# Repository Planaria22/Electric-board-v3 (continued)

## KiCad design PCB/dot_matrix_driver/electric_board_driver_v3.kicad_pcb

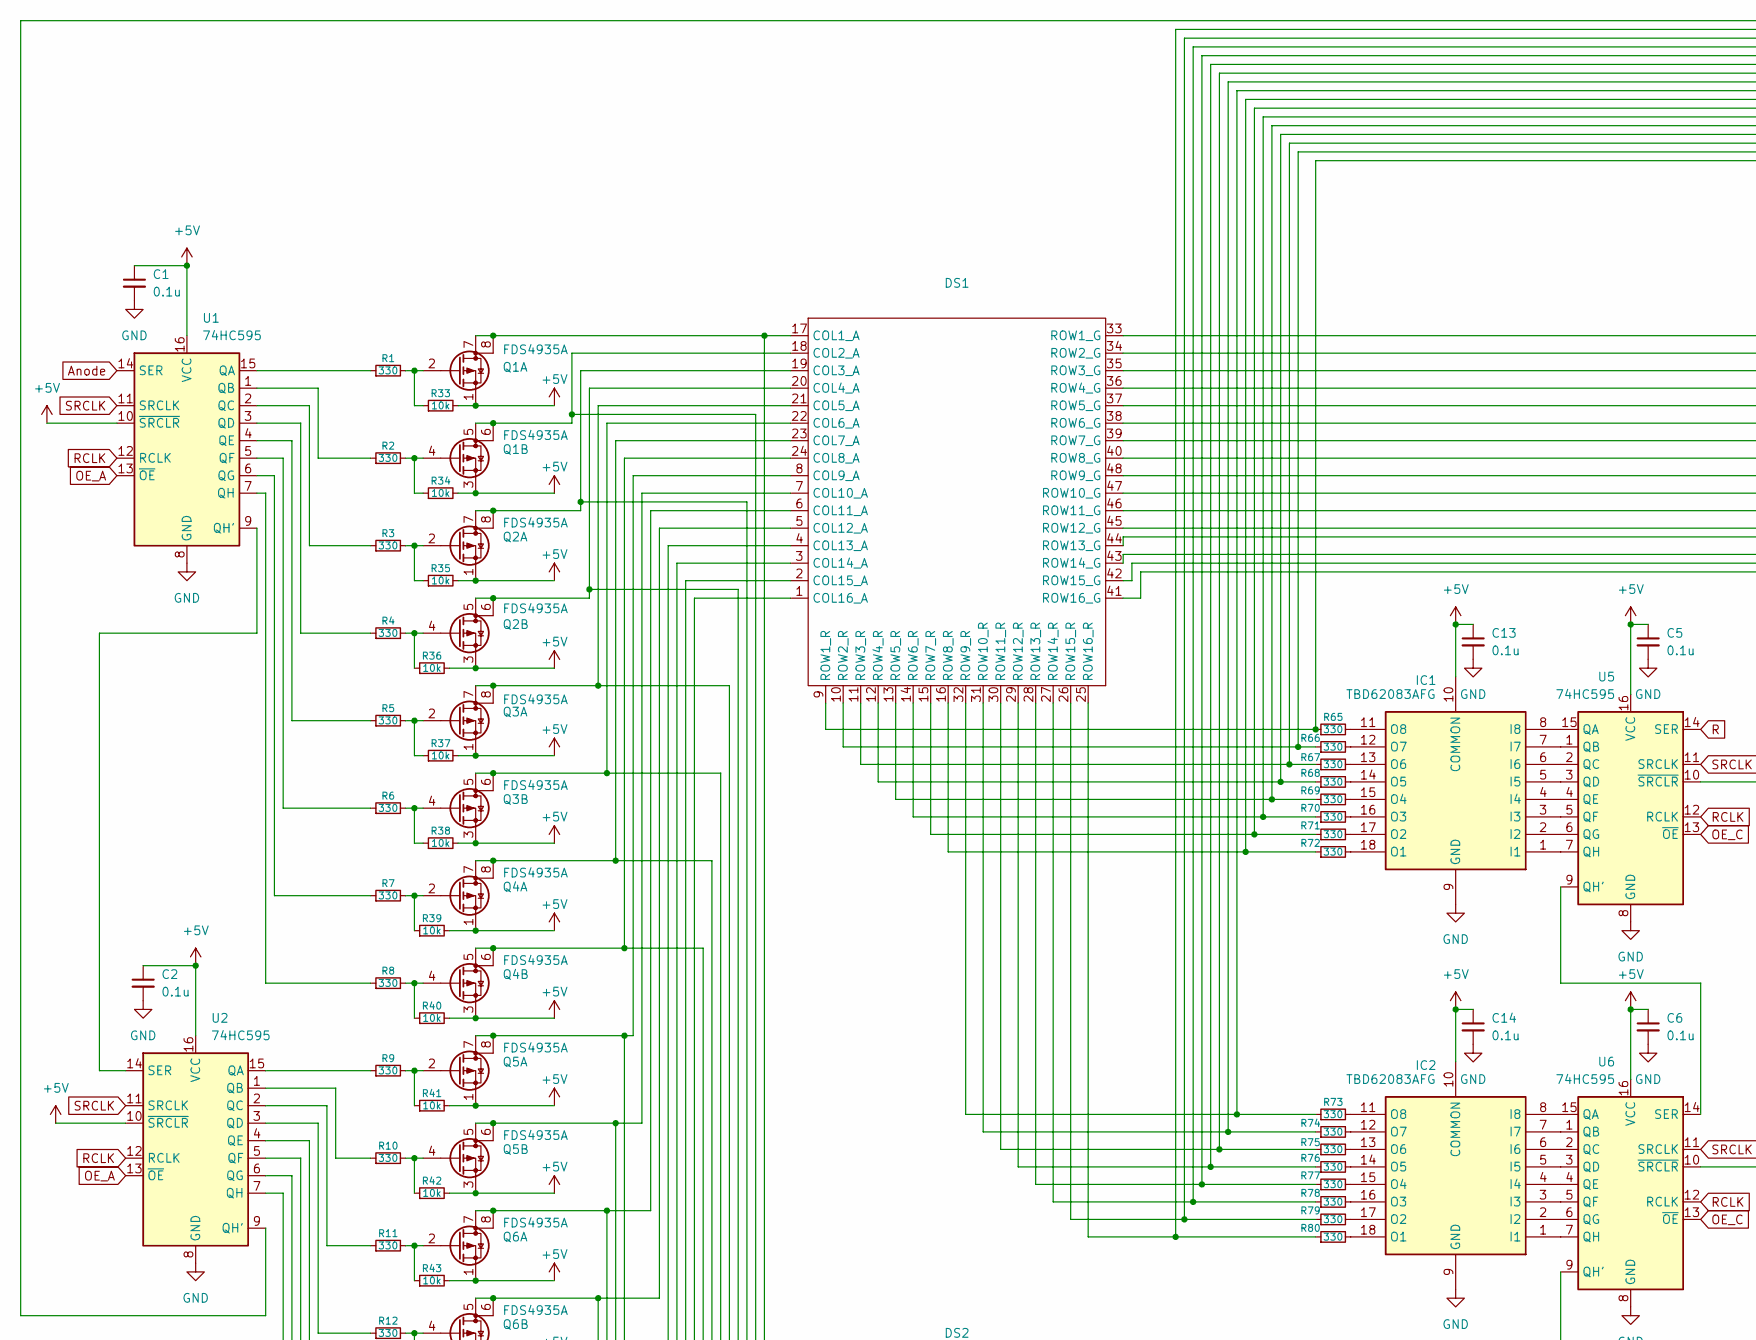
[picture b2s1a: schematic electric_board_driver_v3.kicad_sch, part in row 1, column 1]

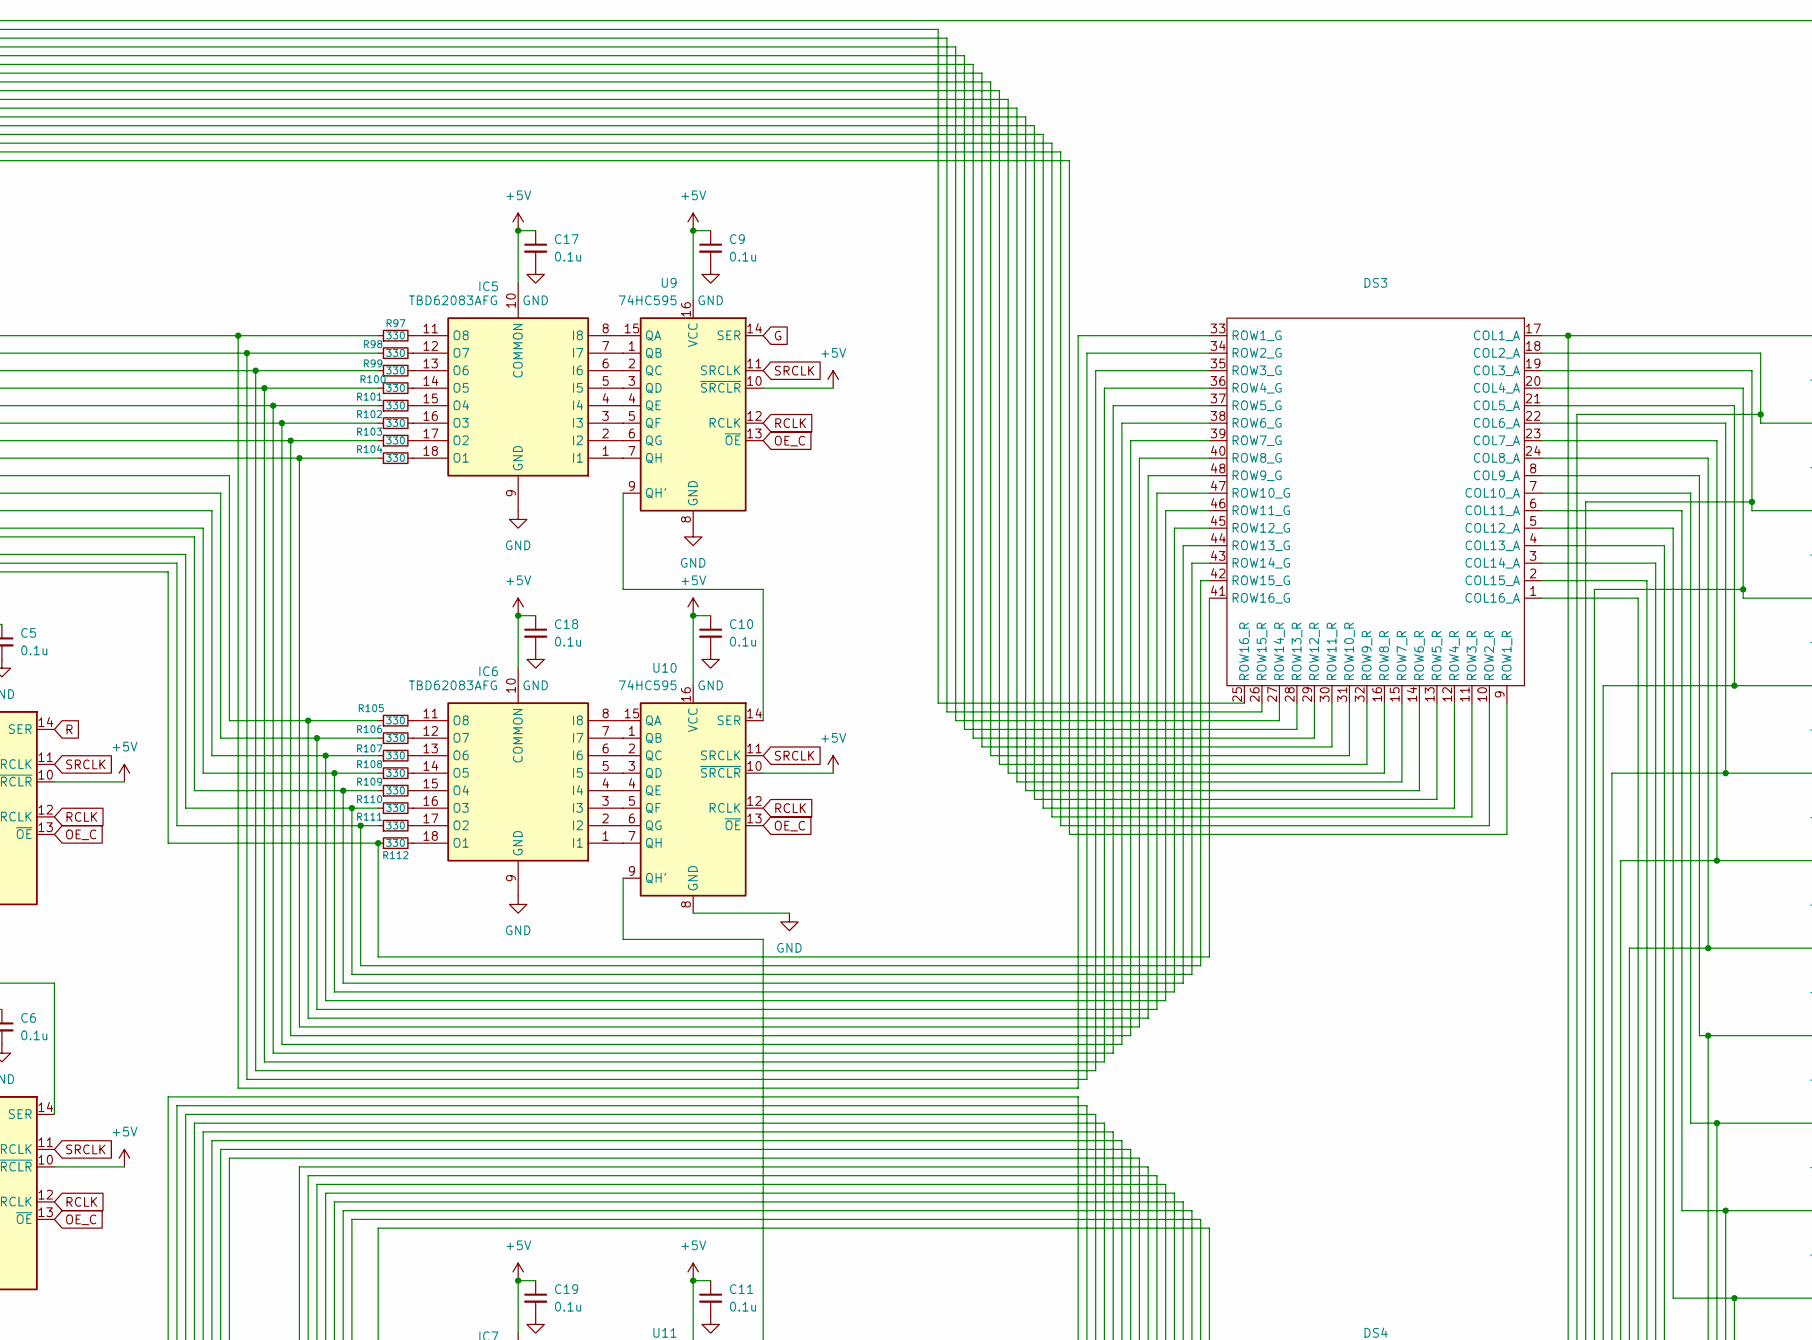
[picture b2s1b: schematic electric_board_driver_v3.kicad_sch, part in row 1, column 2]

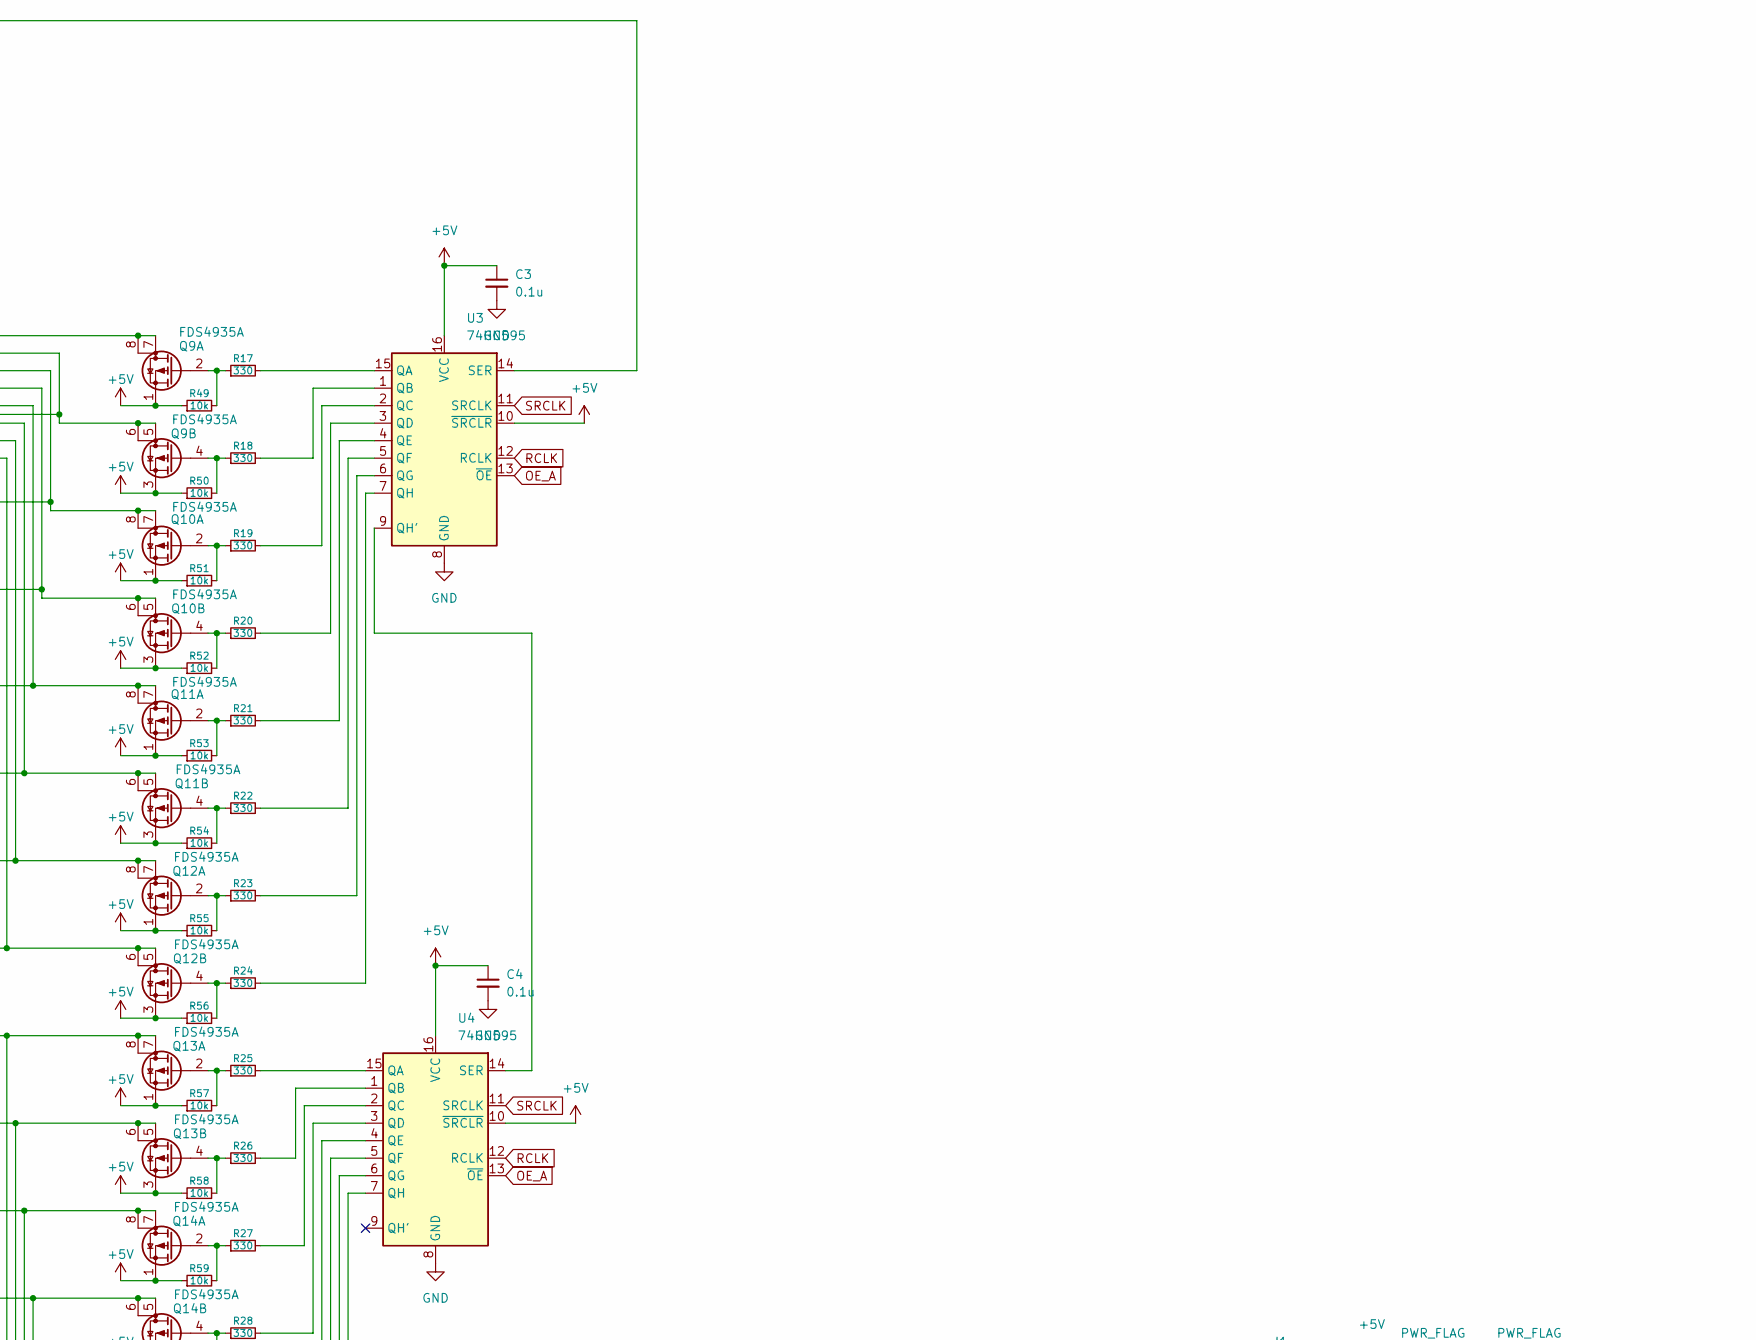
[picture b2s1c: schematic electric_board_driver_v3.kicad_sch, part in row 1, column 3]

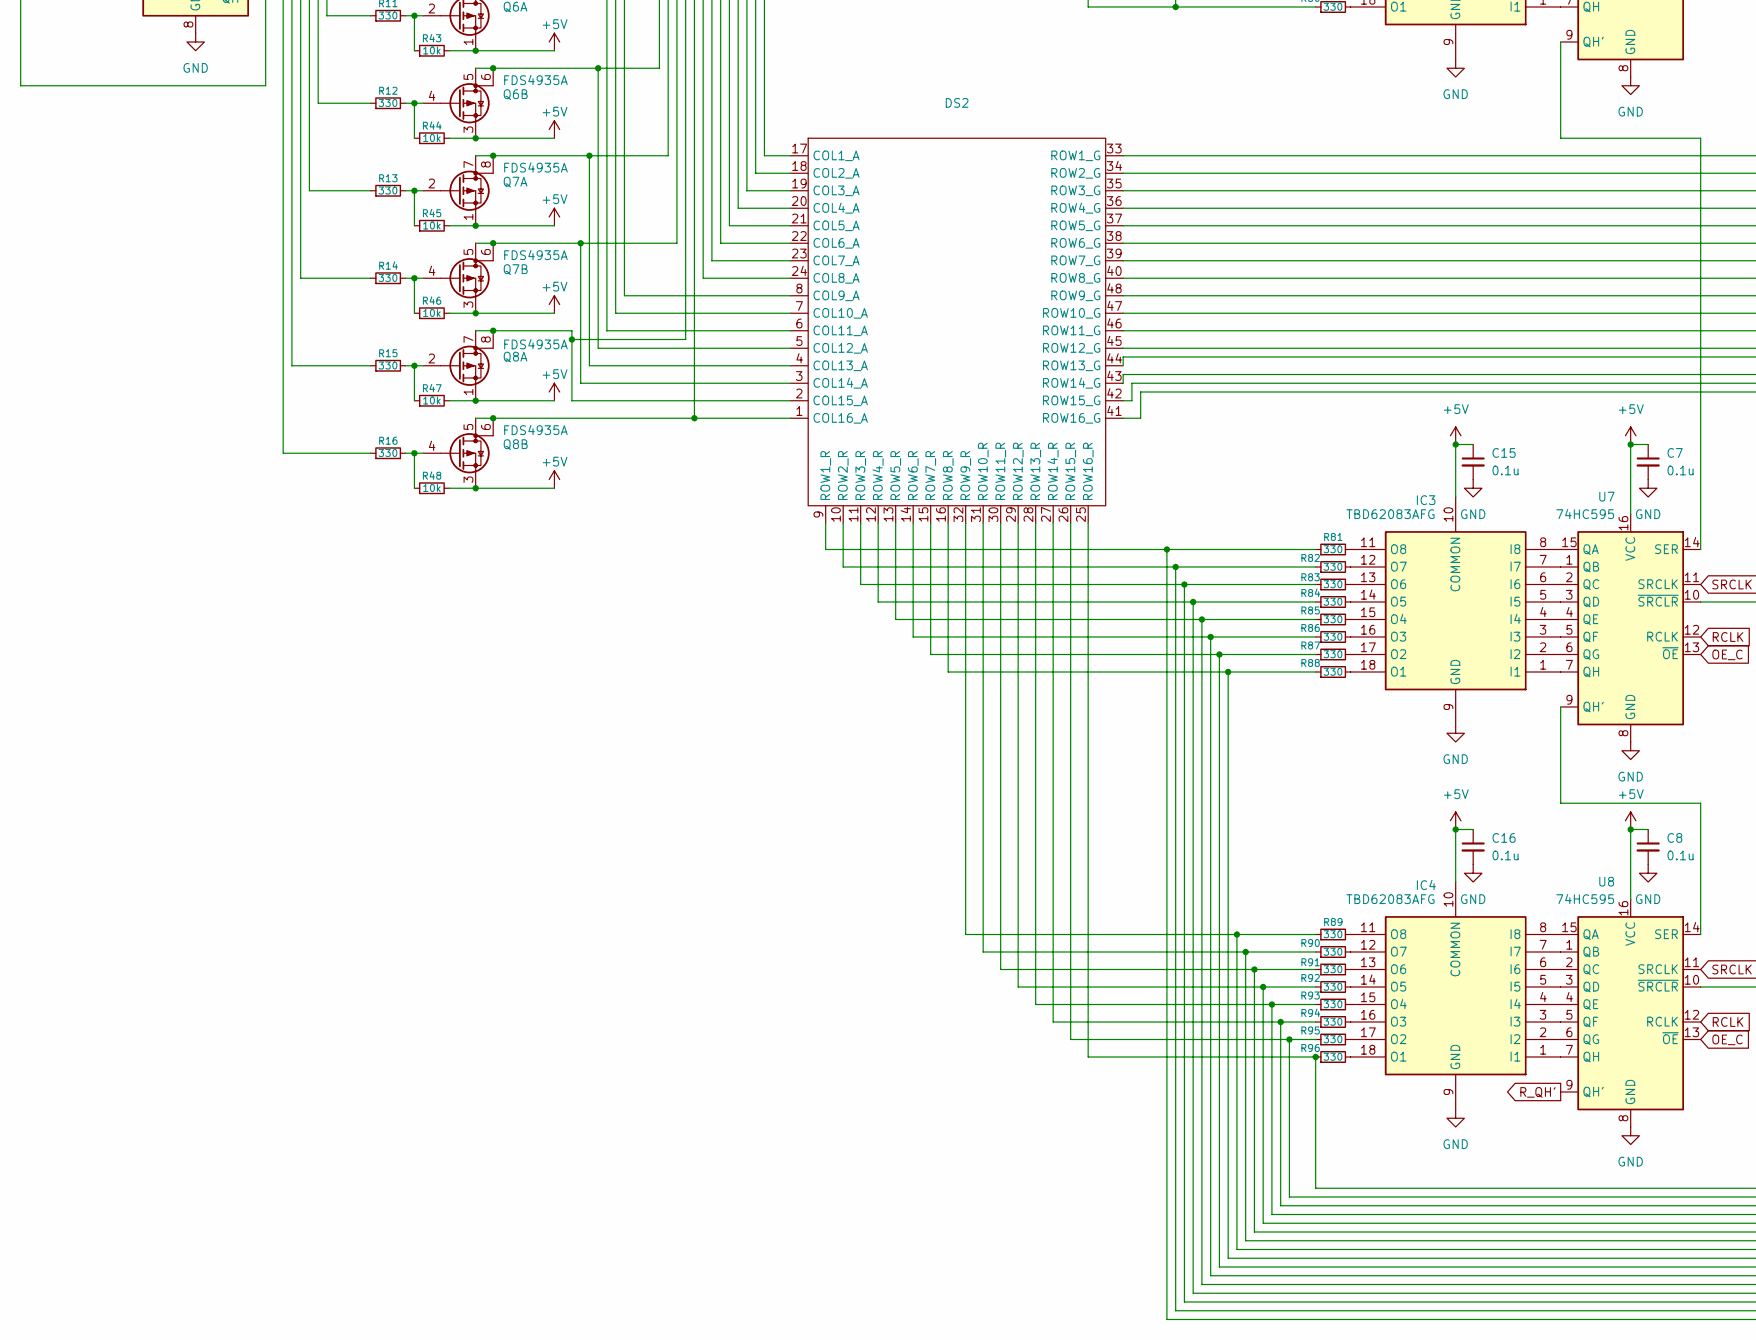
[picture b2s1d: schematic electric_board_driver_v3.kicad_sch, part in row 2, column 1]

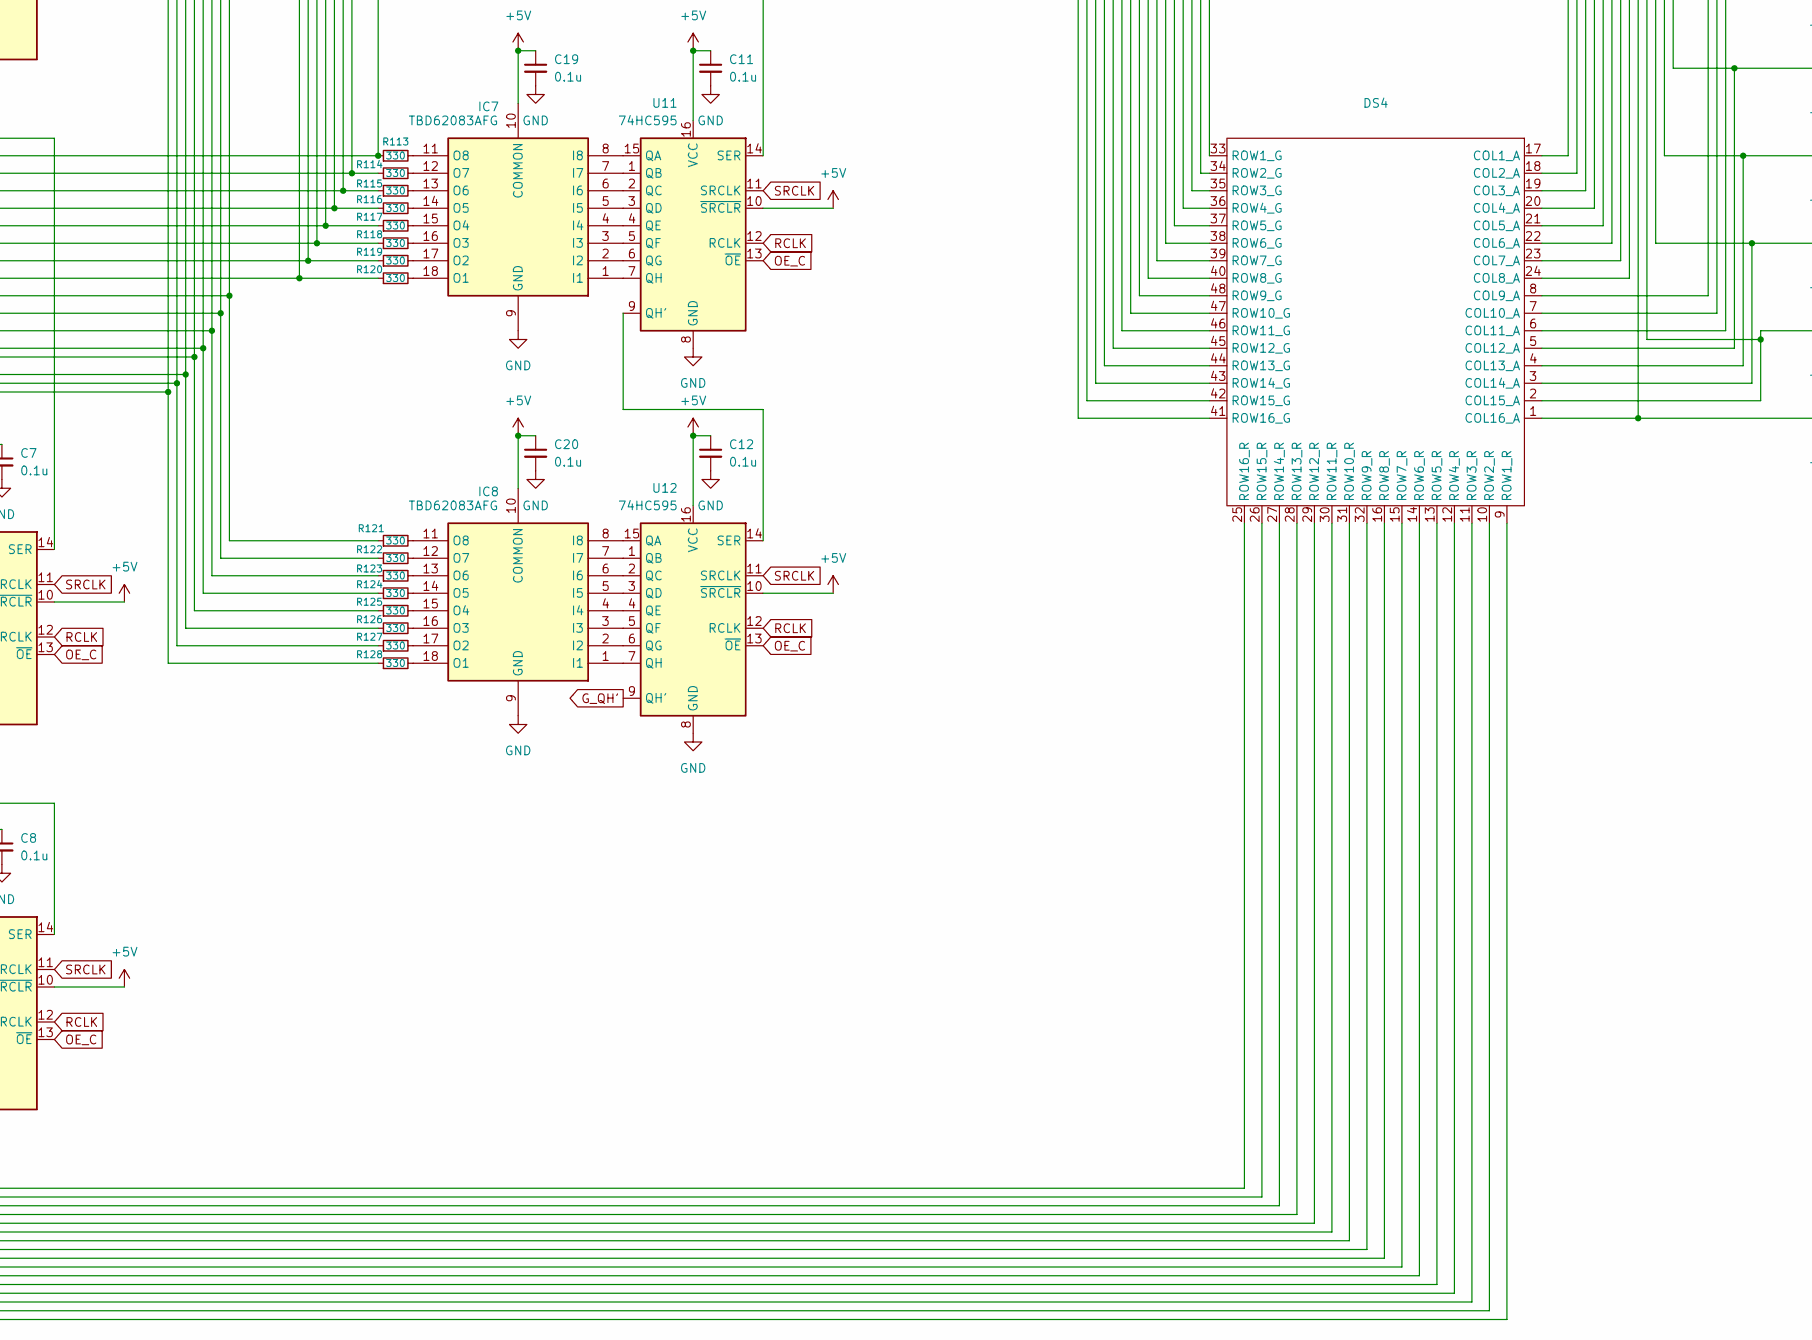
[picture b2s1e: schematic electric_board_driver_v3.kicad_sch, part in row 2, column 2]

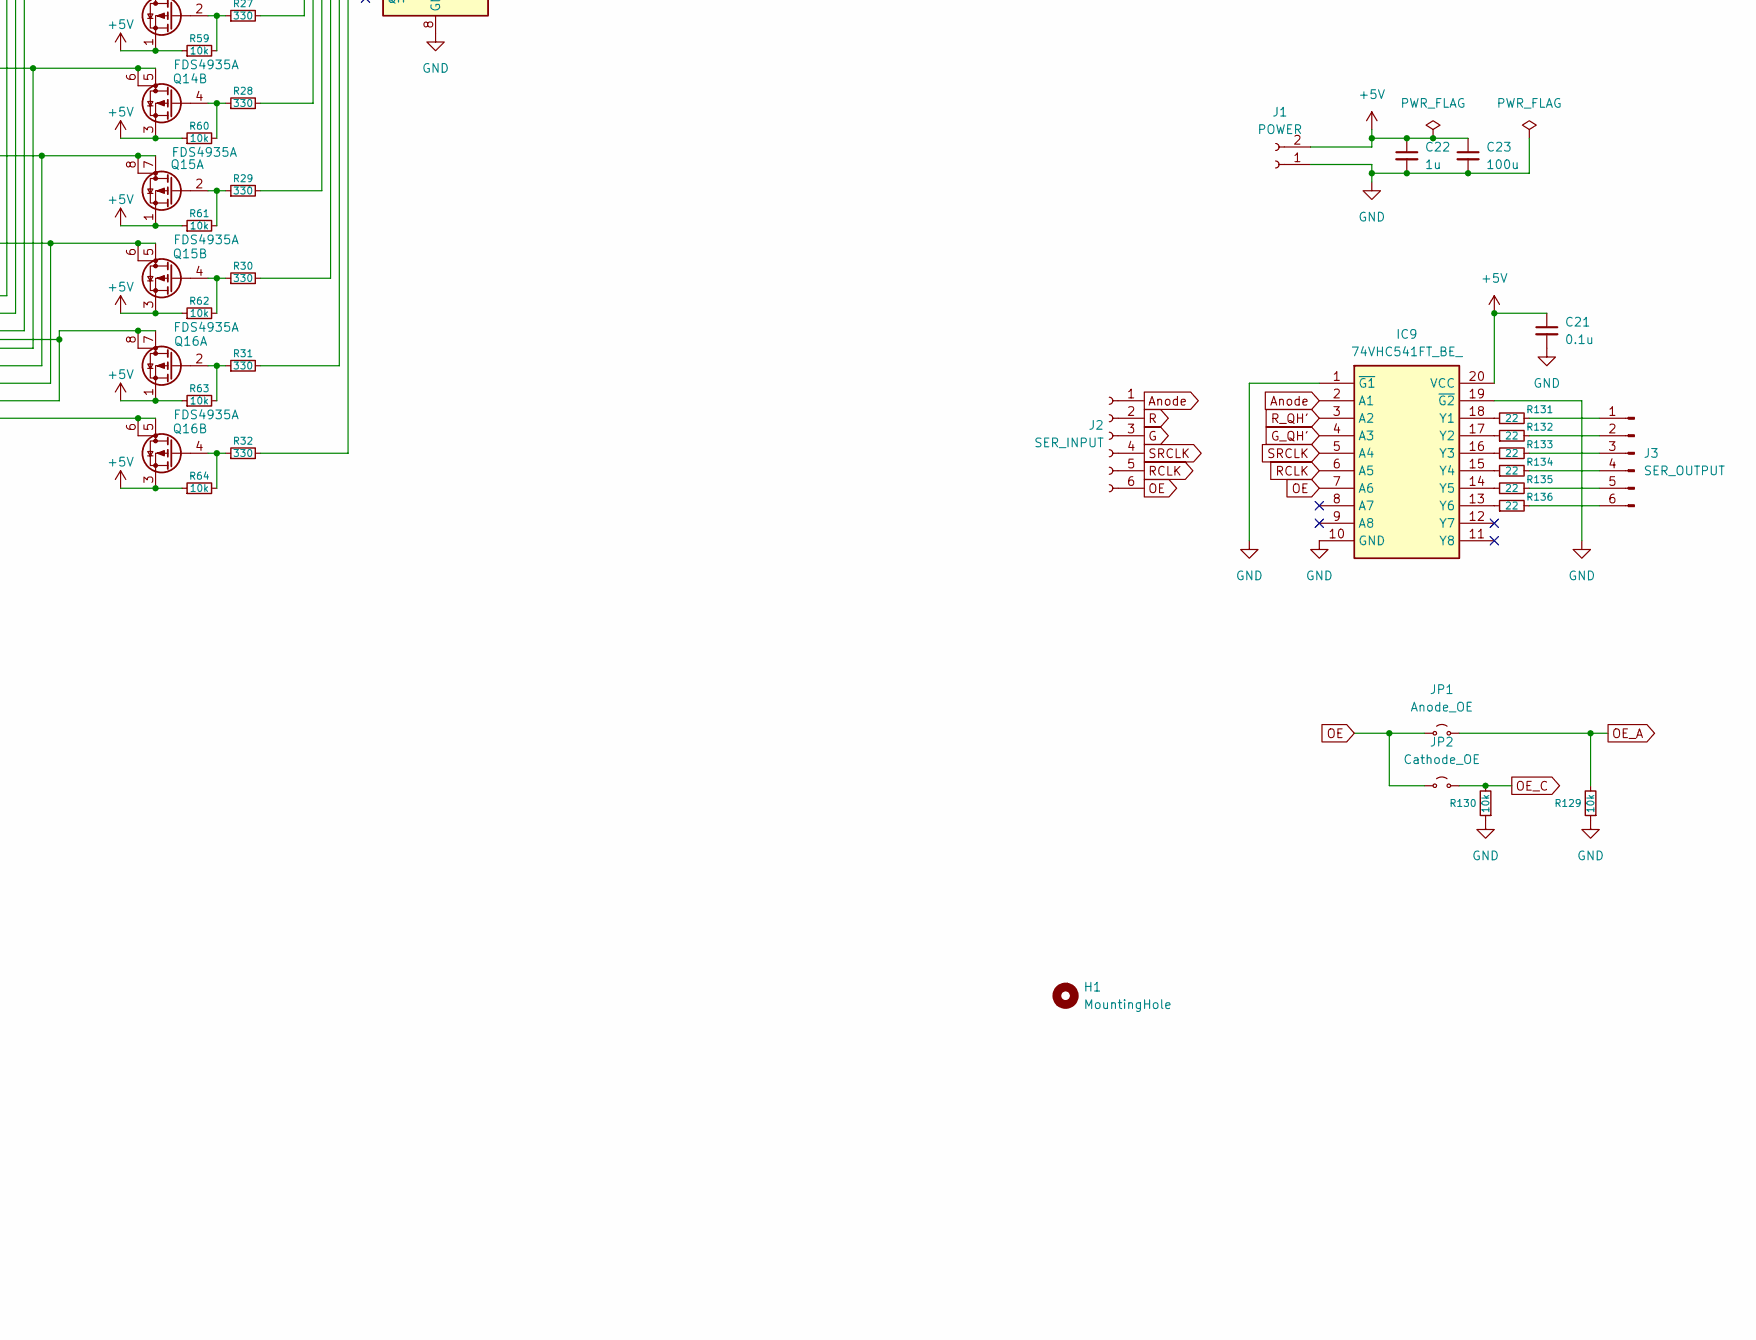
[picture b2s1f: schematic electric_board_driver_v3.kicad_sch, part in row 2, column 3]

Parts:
C1, C2, C3, C4, C5, C6, C7, C8, C9, C10, C11, C12, C13, C14, C15, C16, C17, C18, C19, C20, C21: 0.1u; C_0603_1608Metric
C22: 1u; C_Disc_D5.0mm_W2.5mm_P5.00mm
C23: 100u; CP_Radial_D5.0mm_P2.00mm
DS1, DS2, DS3, DS4: MD1516
H1: MountingHole; MountingHole_3.2mm_M3
IC1, IC2, IC3, IC4, IC5, IC6, IC7, IC8: TBD62083AFG; TBD62083AFNG; Manufacturer_Part_Number TBD62083AFG; Mouser Part Number N/A
IC9: 74VHC541FT_BE_; 74VHC541FT(BE); Manufacturer_Part_Number 74VHC541FT(BE); Mouser Part Number 757-74VHC541FT(BE)
J1: POWER; JST_VH_B2P-VH_1x02_P3.96mm_Vertical
J2: SER_INPUT; PinSocket_1x06_P2.54mm_Horizontal
J3: SER_OUTPUT; PinHeader_1x06_P2.54mm_Horizontal
JP1: Anode_OE; SolderJumper-2_P1.3mm_Open_RoundedPad1.0x1.5mm
JP2: Cathode_OE; SolderJumper-2_P1.3mm_Open_RoundedPad1.0x1.5mm
Q1, Q2, Q3, Q4, Q5, Q6, Q7, Q8, Q9, Q10, Q11, Q12, Q13, Q14, Q15, Q16: FDS4935A; SOIC-8_3.9x4.9mm_P1.27mm
R1, R2, R3, R4, R5, R6, R7, R8, R9, R10, R11, R12, R13, R14, R15, R16, R17, R18, R19, R20, R21, R22, R23, R24, R25, R26, R27, R28, R29, R30, R31, R32, R65, R66, R67, R68, R69, R70, R71, R72, R73, R74, R75, R76, R77, R78, R79, R80, R81, R82, R83, R84, R85, R86, R87, R88, R89, R90, R91, R92, R93, R94, R95, R96, R97, R98, R99, R100, R101, R102, R103, R104, R105, R106, R107, R108, R109, R110, R111, R112, R113, R114, R115, R116, R117, R118, R119, R120, R121, R122, R123, R124, R125, R126, R127, R128: 330; R_0603_1608Metric
R33, R34, R35, R36, R37, R38, R39, R40, R41, R42, R43, R44, R45, R46, R47, R48, R49, R50, R51, R52, R53, R54, R55, R56, R57, R58, R59, R60, R61, R62, R63, R64, R129, R130: 10k; R_0603_1608Metric
R131, R132, R133, R134, R135, R136: 22; R_0603_1608Metric
U1, U2, U3, U4, U5, U6, U7, U8, U9, U10, U11, U12: 74HC595; MC74HC595ADTR2G

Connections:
+5V: C1.1, C2.1, C3.1, C4.1, C5.1, C6.1, C7.1, C8.1, C9.1, C10.1, C11.1, C12.1, C13.1, C14.1, C15.1, C16.1, C17.1, C18.1, C19.1, C20.1, C21.1, C22.1, C23.1, IC1.10 (COMMON), IC2.10 (COMMON), IC3.10 (COMMON), IC4.10 (COMMON), IC5.10 (COMMON), IC6.10 (COMMON), IC7.10 (COMMON), IC8.10 (COMMON), IC9.20 (VCC), J1.2, Q1.1 (S), Q1.3 (S), Q2.1 (S), Q2.3 (S), Q3.1 (S), Q3.3 (S), Q4.1 (S), Q4.3 (S), Q5.1 (S), Q5.3 (S), Q6.1 (S), Q6.3 (S), Q7.1 (S), Q7.3 (S), Q8.1 (S), Q8.3 (S), Q9.1 (S), Q9.3 (S), Q10.1 (S), Q10.3 (S), Q11.1 (S), Q11.3 (S), Q12.1 (S), Q12.3 (S), Q13.1 (S), Q13.3 (S), Q14.1 (S), Q14.3 (S), Q15.1 (S), Q15.3 (S), Q16.1 (S), Q16.3 (S), R33.2, R34.2, R35.2, R36.2, R37.2, R38.2, R39.2, R40.2, R41.2, R42.2, R43.2, R44.2, R45.2, R46.2, R47.2, R48.2, R49.1, R50.1, R51.1, R52.1, R53.1, R54.1, R55.1, R56.1, R57.1, R58.1, R59.1, R60.1, R61.1, R62.1, R63.1, R64.1, U1.10 (~SRCLR), U1.16 (VCC), U2.10 (~SRCLR), U2.16 (VCC), U3.10 (~SRCLR), U3.16 (VCC), U4.10 (~SRCLR), U4.16 (VCC), U5.10 (~SRCLR), U5.16 (VCC), U6.10 (~SRCLR), U6.16 (VCC), U7.10 (~SRCLR), U7.16 (VCC), U8.10 (~SRCLR), U8.16 (VCC), U9.10 (~SRCLR), U9.16 (VCC), U10.10 (~SRCLR), U10.16 (VCC), U11.10 (~SRCLR), U11.16 (VCC), U12.10 (~SRCLR), U12.16 (VCC)
Anode: IC9.2 (A1), J2.1, U1.14 (SER)
G: J2.3, U9.14 (SER)
GND: C1.2, C2.2, C3.2, C4.2, C5.2, C6.2, C7.2, C8.2, C9.2, C10.2, C11.2, C12.2, C13.2, C14.2, C15.2, C16.2, C17.2, C18.2, C19.2, C20.2, C21.2, C22.2, C23.2, IC1.9 (GND), IC2.9 (GND), IC3.9 (GND), IC4.9 (GND), IC5.9 (GND), IC6.9 (GND), IC7.9 (GND), IC8.9 (GND), IC9.1 (~G1), IC9.10 (GND), IC9.19 (~G2), J1.1, R129.1, R130.1, U1.8 (GND), U2.8 (GND), U3.8 (GND), U4.8 (GND), U5.8 (GND), U6.8 (GND), U7.8 (GND), U8.8 (GND), U9.8 (GND), U10.8 (GND), U11.8 (GND), U12.8 (GND)
G_QH': IC9.4 (A3), U12.9 (QH')
unnamed: DS1.17 (COL1_A), DS2.17 (COL1_A), Q1.7 (D), Q1.8 (D)
unnamed: DS1.18 (COL2_A), DS2.18 (COL2_A), Q1.5 (D), Q1.6 (D)
unnamed: DS1.19 (COL3_A), DS2.19 (COL3_A), Q2.7 (D), Q2.8 (D)
unnamed: DS1.20 (COL4_A), DS2.20 (COL4_A), Q2.5 (D), Q2.6 (D)
unnamed: DS1.21 (COL5_A), DS2.21 (COL5_A), Q3.7 (D), Q3.8 (D)
unnamed: DS1.22 (COL6_A), DS2.22 (COL6_A), Q3.5 (D), Q3.6 (D)
unnamed: DS1.23 (COL7_A), DS2.23 (COL7_A), Q4.7 (D), Q4.8 (D)
unnamed: DS1.24 (COL8_A), DS2.24 (COL8_A), Q4.5 (D), Q4.6 (D)
unnamed: DS1.8 (COL9_A), DS2.8 (COL9_A), Q5.7 (D), Q5.8 (D)
unnamed: DS1.7 (COL10_A), DS2.7 (COL10_A), Q5.5 (D), Q5.6 (D)
unnamed: DS1.6 (COL11_A), DS2.6 (COL11_A), Q6.7 (D), Q6.8 (D)
unnamed: DS1.5 (COL12_A), DS2.5 (COL12_A), Q6.5 (D), Q6.6 (D)
unnamed: DS1.4 (COL13_A), DS2.4 (COL13_A), Q7.7 (D), Q7.8 (D)
unnamed: DS1.3 (COL14_A), DS2.3 (COL14_A), Q7.5 (D), Q7.6 (D)
unnamed: DS1.2 (COL15_A), DS2.2 (COL15_A), Q8.7 (D), Q8.8 (D)
unnamed: DS1.1 (COL16_A), DS2.1 (COL16_A), Q8.5 (D), Q8.6 (D)
unnamed: DS1.33 (ROW1_G), DS3.33 (ROW1_G), R97.1
unnamed: DS1.9 (ROW1_R), DS3.9 (ROW1_R), R65.1
unnamed: DS1.34 (ROW2_G), DS3.34 (ROW2_G), R98.1
unnamed: DS1.10 (ROW2_R), DS3.10 (ROW2_R), R66.1
unnamed: DS1.35 (ROW3_G), DS3.35 (ROW3_G), R99.1
unnamed: DS1.11 (ROW3_R), DS3.11 (ROW3_R), R67.1
unnamed: DS1.36 (ROW4_G), DS3.36 (ROW4_G), R100.1
unnamed: DS1.12 (ROW4_R), DS3.12 (ROW4_R), R68.1
unnamed: DS1.37 (ROW5_G), DS3.37 (ROW5_G), R101.1
unnamed: DS1.13 (ROW5_R), DS3.13 (ROW5_R), R69.1
unnamed: DS1.38 (ROW6_G), DS3.38 (ROW6_G), R102.1
unnamed: DS1.14 (ROW6_R), DS3.14 (ROW6_R), R70.1
unnamed: DS1.39 (ROW7_G), DS3.39 (ROW7_G), R103.1
unnamed: DS1.15 (ROW7_R), DS3.15 (ROW7_R), R71.1
unnamed: DS1.40 (ROW8_G), DS3.40 (ROW8_G), R104.1
unnamed: DS1.16 (ROW8_R), DS3.16 (ROW8_R), R72.1
unnamed: DS1.48 (ROW9_G), DS3.48 (ROW9_G), R105.1
unnamed: DS1.32 (ROW9_R), DS3.32 (ROW9_R), R73.1
unnamed: DS1.47 (ROW10_G), DS3.47 (ROW10_G), R106.1
unnamed: DS1.31 (ROW10_R), DS3.31 (ROW10_R), R74.1
unnamed: DS1.46 (ROW11_G), DS3.46 (ROW11_G), R107.1
unnamed: DS1.30 (ROW11_R), DS3.30 (ROW11_R), R75.1
unnamed: DS1.45 (ROW12_G), DS3.45 (ROW12_G), R108.1
unnamed: DS1.29 (ROW12_R), DS3.29 (ROW12_R), R76.1
unnamed: DS1.44 (ROW13_G), DS3.44 (ROW13_G), R109.1
unnamed: DS1.28 (ROW13_R), DS3.28 (ROW13_R), R77.1
unnamed: DS1.43 (ROW14_G), DS3.43 (ROW14_G), R110.1
unnamed: DS1.27 (ROW14_R), DS3.27 (ROW14_R), R78.1
unnamed: DS1.42 (ROW15_G), DS3.42 (ROW15_G), R111.1
unnamed: DS1.26 (ROW15_R), DS3.26 (ROW15_R), R79.1
unnamed: DS1.41 (ROW16_G), DS3.41 (ROW16_G), R112.1
unnamed: DS1.25 (ROW16_R), DS3.25 (ROW16_R), R80.1
unnamed: DS2.33 (ROW1_G), DS4.33 (ROW1_G), R113.1
unnamed: DS2.9 (ROW1_R), DS4.9 (ROW1_R), R81.1
unnamed: DS2.34 (ROW2_G), DS4.34 (ROW2_G), R114.1
unnamed: DS2.10 (ROW2_R), DS4.10 (ROW2_R), R82.1
unnamed: DS2.35 (ROW3_G), DS4.35 (ROW3_G), R115.1
unnamed: DS2.11 (ROW3_R), DS4.11 (ROW3_R), R83.1
unnamed: DS2.36 (ROW4_G), DS4.36 (ROW4_G), R116.1
unnamed: DS2.12 (ROW4_R), DS4.12 (ROW4_R), R84.1
unnamed: DS2.37 (ROW5_G), DS4.37 (ROW5_G), R117.1
unnamed: DS2.13 (ROW5_R), DS4.13 (ROW5_R), R85.1
unnamed: DS2.38 (ROW6_G), DS4.38 (ROW6_G), R118.1
unnamed: DS2.14 (ROW6_R), DS4.14 (ROW6_R), R86.1
unnamed: DS2.39 (ROW7_G), DS4.39 (ROW7_G), R119.1
unnamed: DS2.15 (ROW7_R), DS4.15 (ROW7_R), R87.1
unnamed: DS2.40 (ROW8_G), DS4.40 (ROW8_G), R120.1
unnamed: DS2.16 (ROW8_R), DS4.16 (ROW8_R), R88.1
unnamed: DS2.48 (ROW9_G), DS4.48 (ROW9_G), R121.1
unnamed: DS2.32 (ROW9_R), DS4.32 (ROW9_R), R89.1
unnamed: DS2.47 (ROW10_G), DS4.47 (ROW10_G), R122.1
unnamed: DS2.31 (ROW10_R), DS4.31 (ROW10_R), R90.1
unnamed: DS2.46 (ROW11_G), DS4.46 (ROW11_G), R123.1
unnamed: DS2.30 (ROW11_R), DS4.30 (ROW11_R), R91.1
unnamed: DS2.45 (ROW12_G), DS4.45 (ROW12_G), R124.1
unnamed: DS2.29 (ROW12_R), DS4.29 (ROW12_R), R92.1
unnamed: DS2.44 (ROW13_G), DS4.44 (ROW13_G), R125.1
unnamed: DS2.28 (ROW13_R), DS4.28 (ROW13_R), R93.1
unnamed: DS2.43 (ROW14_G), DS4.43 (ROW14_G), R126.1
unnamed: DS2.27 (ROW14_R), DS4.27 (ROW14_R), R94.1
unnamed: DS2.42 (ROW15_G), DS4.42 (ROW15_G), R127.1
unnamed: DS2.26 (ROW15_R), DS4.26 (ROW15_R), R95.1
unnamed: DS2.41 (ROW16_G), DS4.41 (ROW16_G), R128.1
unnamed: DS2.25 (ROW16_R), DS4.25 (ROW16_R), R96.1
unnamed: DS3.17 (COL1_A), DS4.17 (COL1_A), Q9.7 (D), Q9.8 (D)
unnamed: DS3.18 (COL2_A), DS4.18 (COL2_A), Q9.5 (D), Q9.6 (D)
unnamed: DS3.19 (COL3_A), DS4.19 (COL3_A), Q10.7 (D), Q10.8 (D)
unnamed: DS3.20 (COL4_A), DS4.20 (COL4_A), Q10.5 (D), Q10.6 (D)
unnamed: DS3.21 (COL5_A), DS4.21 (COL5_A), Q11.7 (D), Q11.8 (D)
unnamed: DS3.22 (COL6_A), DS4.22 (COL6_A), Q11.5 (D), Q11.6 (D)
unnamed: DS3.23 (COL7_A), DS4.23 (COL7_A), Q12.7 (D), Q12.8 (D)
unnamed: DS3.24 (COL8_A), DS4.24 (COL8_A), Q12.5 (D), Q12.6 (D)
unnamed: DS3.8 (COL9_A), DS4.8 (COL9_A), Q13.7 (D), Q13.8 (D)
unnamed: DS3.7 (COL10_A), DS4.7 (COL10_A), Q13.5 (D), Q13.6 (D)
unnamed: DS3.6 (COL11_A), DS4.6 (COL11_A), Q14.7 (D), Q14.8 (D)
unnamed: DS3.5 (COL12_A), DS4.5 (COL12_A), Q14.5 (D), Q14.6 (D)
unnamed: DS3.4 (COL13_A), DS4.4 (COL13_A), Q15.7 (D), Q15.8 (D)
unnamed: DS3.3 (COL14_A), DS4.3 (COL14_A), Q15.5 (D), Q15.6 (D)
unnamed: DS3.2 (COL15_A), DS4.2 (COL15_A), Q16.7 (D), Q16.8 (D)
unnamed: DS3.1 (COL16_A), DS4.1 (COL16_A), Q16.5 (D), Q16.6 (D)
unnamed: IC1.1 (I1), U5.7 (QH)
unnamed: IC1.2 (I2), U5.6 (QG)
unnamed: IC1.3 (I3), U5.5 (QF)
unnamed: IC1.4 (I4), U5.4 (QE)
unnamed: IC1.5 (I5), U5.3 (QD)
unnamed: IC1.6 (I6), U5.2 (QC)
unnamed: IC1.7 (I7), U5.1 (QB)
unnamed: IC1.8 (I8), U5.15 (QA)
unnamed: IC1.18 (O1), R72.2
unnamed: IC1.17 (O2), R71.2
unnamed: IC1.16 (O3), R70.2
unnamed: IC1.15 (O4), R69.2
unnamed: IC1.14 (O5), R68.2
unnamed: IC1.13 (O6), R67.2
unnamed: IC1.12 (O7), R66.2
unnamed: IC1.11 (O8), R65.2
unnamed: IC2.1 (I1), U6.7 (QH)
unnamed: IC2.2 (I2), U6.6 (QG)
unnamed: IC2.3 (I3), U6.5 (QF)
unnamed: IC2.4 (I4), U6.4 (QE)
unnamed: IC2.5 (I5), U6.3 (QD)
unnamed: IC2.6 (I6), U6.2 (QC)
unnamed: IC2.7 (I7), U6.1 (QB)
unnamed: IC2.8 (I8), U6.15 (QA)
unnamed: IC2.18 (O1), R80.2
unnamed: IC2.17 (O2), R79.2
unnamed: IC2.16 (O3), R78.2
unnamed: IC2.15 (O4), R77.2
unnamed: IC2.14 (O5), R76.2
unnamed: IC2.13 (O6), R75.2
unnamed: IC2.12 (O7), R74.2
unnamed: IC2.11 (O8), R73.2
unnamed: IC3.1 (I1), U7.7 (QH)
unnamed: IC3.2 (I2), U7.6 (QG)
unnamed: IC3.3 (I3), U7.5 (QF)
unnamed: IC3.4 (I4), U7.4 (QE)
unnamed: IC3.5 (I5), U7.3 (QD)
unnamed: IC3.6 (I6), U7.2 (QC)
unnamed: IC3.7 (I7), U7.1 (QB)
unnamed: IC3.8 (I8), U7.15 (QA)
unnamed: IC3.18 (O1), R88.2
unnamed: IC3.17 (O2), R87.2
unnamed: IC3.16 (O3), R86.2
unnamed: IC3.15 (O4), R85.2
unnamed: IC3.14 (O5), R84.2
unnamed: IC3.13 (O6), R83.2
unnamed: IC3.12 (O7), R82.2
unnamed: IC3.11 (O8), R81.2
unnamed: IC4.1 (I1), U8.7 (QH)
unnamed: IC4.2 (I2), U8.6 (QG)
unnamed: IC4.3 (I3), U8.5 (QF)
unnamed: IC4.4 (I4), U8.4 (QE)
unnamed: IC4.5 (I5), U8.3 (QD)
unnamed: IC4.6 (I6), U8.2 (QC)
unnamed: IC4.7 (I7), U8.1 (QB)
unnamed: IC4.8 (I8), U8.15 (QA)
unnamed: IC4.18 (O1), R96.2
unnamed: IC4.17 (O2), R95.2
unnamed: IC4.16 (O3), R94.2
unnamed: IC4.15 (O4), R93.2
unnamed: IC4.14 (O5), R92.2
unnamed: IC4.13 (O6), R91.2
unnamed: IC4.12 (O7), R90.2
unnamed: IC4.11 (O8), R89.2
unnamed: IC5.1 (I1), U9.7 (QH)
unnamed: IC5.2 (I2), U9.6 (QG)
unnamed: IC5.3 (I3), U9.5 (QF)
unnamed: IC5.4 (I4), U9.4 (QE)
unnamed: IC5.5 (I5), U9.3 (QD)
unnamed: IC5.6 (I6), U9.2 (QC)
unnamed: IC5.7 (I7), U9.1 (QB)
unnamed: IC5.8 (I8), U9.15 (QA)
unnamed: IC5.18 (O1), R104.2
unnamed: IC5.17 (O2), R103.2
unnamed: IC5.16 (O3), R102.2
unnamed: IC5.15 (O4), R101.2
unnamed: IC5.14 (O5), R100.2
unnamed: IC5.13 (O6), R99.2
unnamed: IC5.12 (O7), R98.2
unnamed: IC5.11 (O8), R97.2
unnamed: IC6.1 (I1), U10.7 (QH)
unnamed: IC6.2 (I2), U10.6 (QG)
unnamed: IC6.3 (I3), U10.5 (QF)
unnamed: IC6.4 (I4), U10.4 (QE)
unnamed: IC6.5 (I5), U10.3 (QD)
unnamed: IC6.6 (I6), U10.2 (QC)
unnamed: IC6.7 (I7), U10.1 (QB)
unnamed: IC6.8 (I8), U10.15 (QA)
unnamed: IC6.18 (O1), R112.2
unnamed: IC6.17 (O2), R111.2
unnamed: IC6.16 (O3), R110.2
unnamed: IC6.15 (O4), R109.2
unnamed: IC6.14 (O5), R108.2
unnamed: IC6.13 (O6), R107.2
unnamed: IC6.12 (O7), R106.2
unnamed: IC6.11 (O8), R105.2
unnamed: IC7.1 (I1), U11.7 (QH)
unnamed: IC7.2 (I2), U11.6 (QG)
unnamed: IC7.3 (I3), U11.5 (QF)
unnamed: IC7.4 (I4), U11.4 (QE)
unnamed: IC7.5 (I5), U11.3 (QD)
unnamed: IC7.6 (I6), U11.2 (QC)
unnamed: IC7.7 (I7), U11.1 (QB)
unnamed: IC7.8 (I8), U11.15 (QA)
unnamed: IC7.18 (O1), R120.2
unnamed: IC7.17 (O2), R119.2
unnamed: IC7.16 (O3), R118.2
unnamed: IC7.15 (O4), R117.2
unnamed: IC7.14 (O5), R116.2
unnamed: IC7.13 (O6), R115.2
unnamed: IC7.12 (O7), R114.2
unnamed: IC7.11 (O8), R113.2
unnamed: IC8.1 (I1), U12.7 (QH)
unnamed: IC8.2 (I2), U12.6 (QG)
unnamed: IC8.3 (I3), U12.5 (QF)
unnamed: IC8.4 (I4), U12.4 (QE)
unnamed: IC8.5 (I5), U12.3 (QD)
unnamed: IC8.6 (I6), U12.2 (QC)
unnamed: IC8.7 (I7), U12.1 (QB)
unnamed: IC8.8 (I8), U12.15 (QA)
unnamed: IC8.18 (O1), R128.2
unnamed: IC8.17 (O2), R127.2
unnamed: IC8.16 (O3), R126.2
unnamed: IC8.15 (O4), R125.2
unnamed: IC8.14 (O5), R124.2
unnamed: IC8.13 (O6), R123.2
unnamed: IC8.12 (O7), R122.2
unnamed: IC8.11 (O8), R121.2
unnamed: IC9.18 (Y1), R131.1
unnamed: IC9.17 (Y2), R132.1
unnamed: IC9.16 (Y3), R133.1
unnamed: IC9.15 (Y4), R134.1
unnamed: IC9.14 (Y5), R135.1
unnamed: IC9.13 (Y6), R136.1
unnamed: J3.1, R131.2
unnamed: J3.2, R132.2
unnamed: J3.3, R133.2
unnamed: J3.4, R134.2
unnamed: J3.5, R135.2
unnamed: J3.6, R136.2
unnamed: Q1.2 (G), R1.2, R33.1
unnamed: Q1.4 (G), R2.2, R34.1
unnamed: Q2.2 (G), R3.2, R35.1
unnamed: Q2.4 (G), R4.2, R36.1
unnamed: Q3.2 (G), R5.2, R37.1
unnamed: Q3.4 (G), R6.2, R38.1
unnamed: Q4.2 (G), R7.2, R39.1
unnamed: Q4.4 (G), R8.2, R40.1
unnamed: Q5.2 (G), R9.2, R41.1
unnamed: Q5.4 (G), R10.2, R42.1
unnamed: Q6.2 (G), R11.2, R43.1
unnamed: Q6.4 (G), R12.2, R44.1
unnamed: Q7.2 (G), R13.2, R45.1
unnamed: Q7.4 (G), R14.2, R46.1
unnamed: Q8.2 (G), R15.2, R47.1
unnamed: Q8.4 (G), R16.2, R48.1
unnamed: Q9.2 (G), R17.1, R49.2
unnamed: Q9.4 (G), R18.1, R50.2
unnamed: Q10.2 (G), R19.1, R51.2
unnamed: Q10.4 (G), R20.1, R52.2
unnamed: Q11.2 (G), R21.1, R53.2
unnamed: Q11.4 (G), R22.1, R54.2
unnamed: Q12.2 (G), R23.1, R55.2
unnamed: Q12.4 (G), R24.1, R56.2
unnamed: Q13.2 (G), R25.1, R57.2
unnamed: Q13.4 (G), R26.1, R58.2
unnamed: Q14.2 (G), R27.1, R59.2
unnamed: Q14.4 (G), R28.1, R60.2
unnamed: Q15.2 (G), R29.1, R61.2
unnamed: Q15.4 (G), R30.1, R62.2
unnamed: Q16.2 (G), R31.1, R63.2
unnamed: Q16.4 (G), R32.1, R64.2
unnamed: R1.1, U1.15 (QA)
unnamed: R2.1, U1.1 (QB)
unnamed: R3.1, U1.2 (QC)
unnamed: R4.1, U1.3 (QD)
unnamed: R5.1, U1.4 (QE)
unnamed: R6.1, U1.5 (QF)
unnamed: R7.1, U1.6 (QG)
unnamed: U1.9 (QH'), U2.14 (SER)
unnamed: R8.1, U1.7 (QH)
unnamed: R9.1, U2.15 (QA)
unnamed: R10.1, U2.1 (QB)
unnamed: R11.1, U2.2 (QC)
unnamed: R12.1, U2.3 (QD)
unnamed: R13.1, U2.4 (QE)
unnamed: R14.1, U2.5 (QF)
unnamed: R15.1, U2.6 (QG)
unnamed: U2.9 (QH'), U3.14 (SER)
unnamed: R16.1, U2.7 (QH)
unnamed: R17.2, U3.15 (QA)
unnamed: R18.2, U3.1 (QB)
unnamed: R19.2, U3.2 (QC)
unnamed: R20.2, U3.3 (QD)
unnamed: R21.2, U3.4 (QE)
unnamed: R22.2, U3.5 (QF)
unnamed: R23.2, U3.6 (QG)
unnamed: U3.9 (QH'), U4.14 (SER)
unnamed: R24.2, U3.7 (QH)
unnamed: R25.2, U4.15 (QA)
unnamed: R26.2, U4.1 (QB)
unnamed: R27.2, U4.2 (QC)
unnamed: R28.2, U4.3 (QD)
unnamed: R29.2, U4.4 (QE)
unnamed: R30.2, U4.5 (QF)
unnamed: R31.2, U4.6 (QG)
unnamed: R32.2, U4.7 (QH)
unnamed: U5.9 (QH'), U6.14 (SER)
unnamed: U6.9 (QH'), U7.14 (SER)
unnamed: U7.9 (QH'), U8.14 (SER)
unnamed: U10.9 (QH'), U11.14 (SER)
unnamed: U9.9 (QH'), U10.14 (SER)
unnamed: U11.9 (QH'), U12.14 (SER)
OE: IC9.7 (A6), J2.6, JP1.1 (A), JP2.1 (A)
OE_A: JP1.2 (B), R129.2, U1.13 (~OE), U2.13 (~OE), U3.13 (~OE), U4.13 (~OE)
OE_C: JP2.2 (B), R130.2, U5.13 (~OE), U6.13 (~OE), U7.13 (~OE), U8.13 (~OE), U9.13 (~OE), U10.13 (~OE), U11.13 (~OE), U12.13 (~OE)
R: J2.2, U5.14 (SER)
RCLK: IC9.6 (A5), J2.5, U1.12 (RCLK), U2.12 (RCLK), U3.12 (RCLK), U4.12 (RCLK), U5.12 (RCLK), U6.12 (RCLK), U7.12 (RCLK), U8.12 (RCLK), U9.12 (RCLK), U10.12 (RCLK), U11.12 (RCLK), U12.12 (RCLK)
R_QH': IC9.3 (A2), U8.9 (QH')
SRCLK: IC9.5 (A4), J2.4, U1.11 (SRCLK), U2.11 (SRCLK), U3.11 (SRCLK), U4.11 (SRCLK), U5.11 (SRCLK), U6.11 (SRCLK), U7.11 (SRCLK), U8.11 (SRCLK), U9.11 (SRCLK), U10.11 (SRCLK), U11.11 (SRCLK), U12.11 (SRCLK)
